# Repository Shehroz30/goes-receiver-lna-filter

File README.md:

# GOES Receiver

Made a GOES Receiver that operates on 1694.1 MHz, intended to interpret HRIT signals. This is the low noise amplifier and filter portion. 

*PCB Render in KiCAD.*

## BOM:
- QLP9547 Low Noise Amplifier
- RF Coaxial Connectors
- USB-C Port
- Miscellaneous (resistors, inductors, etc)

## Filter Topology:
Designed using ADS, the filter is a 5th order Chebyshev filter based off of a hairpin design, intended to have 80 MHz bandwidth and operate as a bandpass filter. This compacts space and allows for the filter to fit on the PCB (which uses a PTFE Teflon dielectric). However, it does result in some insertion loss as can be seen in the attached graphs plotting S(1,1) and S(2, 1). At 1694.1 MHz, there's around -2.7 dB of insertion loss on S(2,1). Not bad!

*Figure 1: Graph looking at the insertion loss of the filter.*

*Figure 2: Taken from ADS Studio, shows the schematic of the filter based off of microstrip lines.*

*Figure 3: Render of the Chebyshev filter on its own in KiCad.*

## What's left
Currently, software needs to be added and the board needs to be evaluated using a dish to receive the signals. 

## Gratitudes
Worked on with [@xuanmingl0415-arch](https://github.com/xuanmingl0415-arch)

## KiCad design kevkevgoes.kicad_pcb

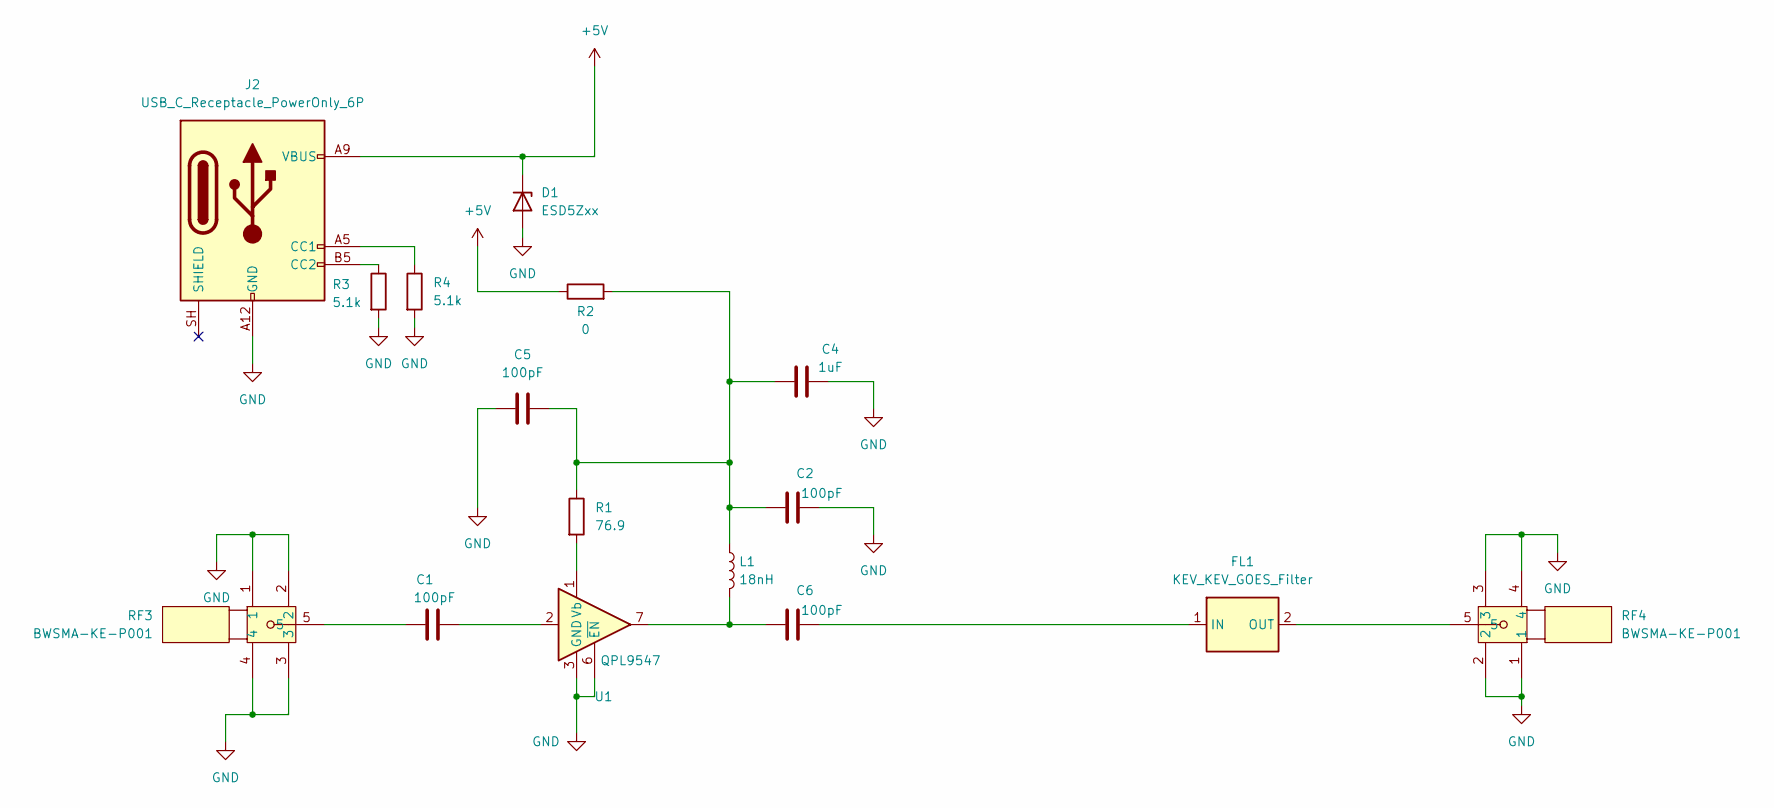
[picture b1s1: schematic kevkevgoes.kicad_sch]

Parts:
C1, C2, C5, C6: 100pF; C_0402_1005Metric
C4: 1uF; C_0402_1005Metric
D1: ESD5Zxx; D_SOD-523
FL1: KEV_KEV_GOES_Filter; Untitled
J2: USB_C_Receptacle_PowerOnly_6P; USB_C_Receptacle_HRO_TYPE-C-31-M-17
L1: 18nH; L_0402_1005Metric
R1: 76.9; R_0402_1005Metric
R2: 0; R_0402_1005Metric
R3, R4: 5.1k; R_0402_1005Metric
RF3, RF4: BWSMA-KE-P001; SMA-SMD_BWSMA-KE-P001; MPN BWSMA-KE-P001; LCSC Part C496550
U1: QPL9547; DFN-8-1EP_2x2mm_P0.5mm_EP1.05x1.75mm; LCSC C5367093

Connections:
+5V: D1.1 (K), J2.A9 (VBUS), J2.B9 (VBUS), R2.1
GND: C2.2, C4.2, C5.1, D1.2 (A), J2.A12 (GND), J2.B12 (GND), R3.2, R4.2, RF3.1, RF3.2, RF3.3, RF3.4, RF4.1, RF4.2, RF4.3, RF4.4, U1.3 (GND), U1.4 (GND), U1.5 (GND), U1.6 (~EN), U1.8 (GND), U1.9 (GND)
unnamed: C1.1, RF3.5
unnamed: C1.2, U1.2
unnamed: C2.1, C4.1, C5.2, L1.1, R1.1, R2.2
unnamed: C6.1, L1.2, U1.7
unnamed: C6.2, FL1.1 (IN)
unnamed: FL1.2 (OUT), RF4.5
unnamed: J2.A5 (CC1), R4.1
unnamed: J2.B5 (CC2), R3.1
unnamed: R1.2, U1.1 (Vb)

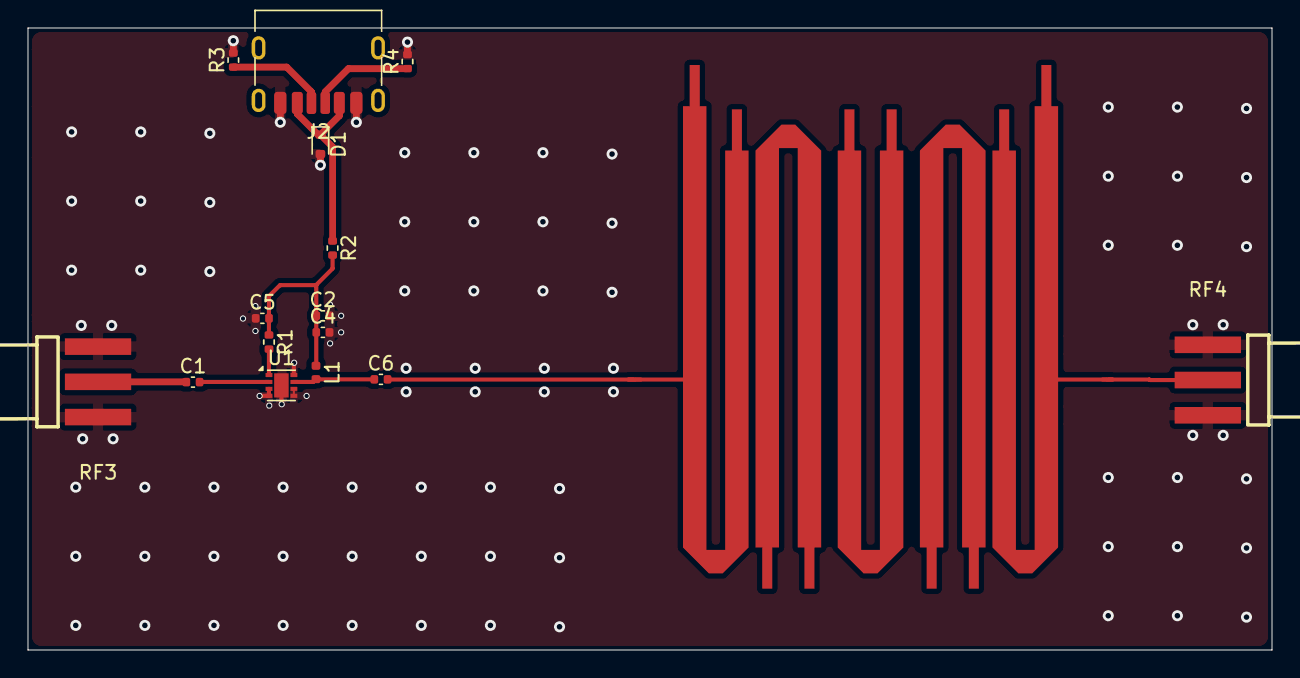
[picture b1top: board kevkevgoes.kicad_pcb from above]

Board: 2 copper layers, 90.0 x 45.0 mm, 16 parts (0 on the bottom side), 11 nets.

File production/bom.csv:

Designator,Footprint,Quantity,Value,LCSC Part #
"C1, C2, C5, C6",0402,4,100pF,
C4,0402,1,1uF,
D1,D_SOD-523,1,ESD5Zxx,
FL1,Untitled,1,KEV_KEV_GOES_Filter,
J2,USB_C_Receptacle_HRO_TYPE-C-31-M-17,1,USB_C_Receptacle_PowerOnly_6P,
L1,0402,1,18nH,
R1,0402,1,76.9,
R2,0402,1,0,
"R3, R4",0402,2,5.1k,
"RF3, RF4",SMA-SMD_BWSMA-KE-P001,2,BWSMA-KE-P001,C496550
U1,DFN-8-1EP_2x2mm_P0.5mm_EP1.05x1.75mm,1,QPL9547,C5367093
